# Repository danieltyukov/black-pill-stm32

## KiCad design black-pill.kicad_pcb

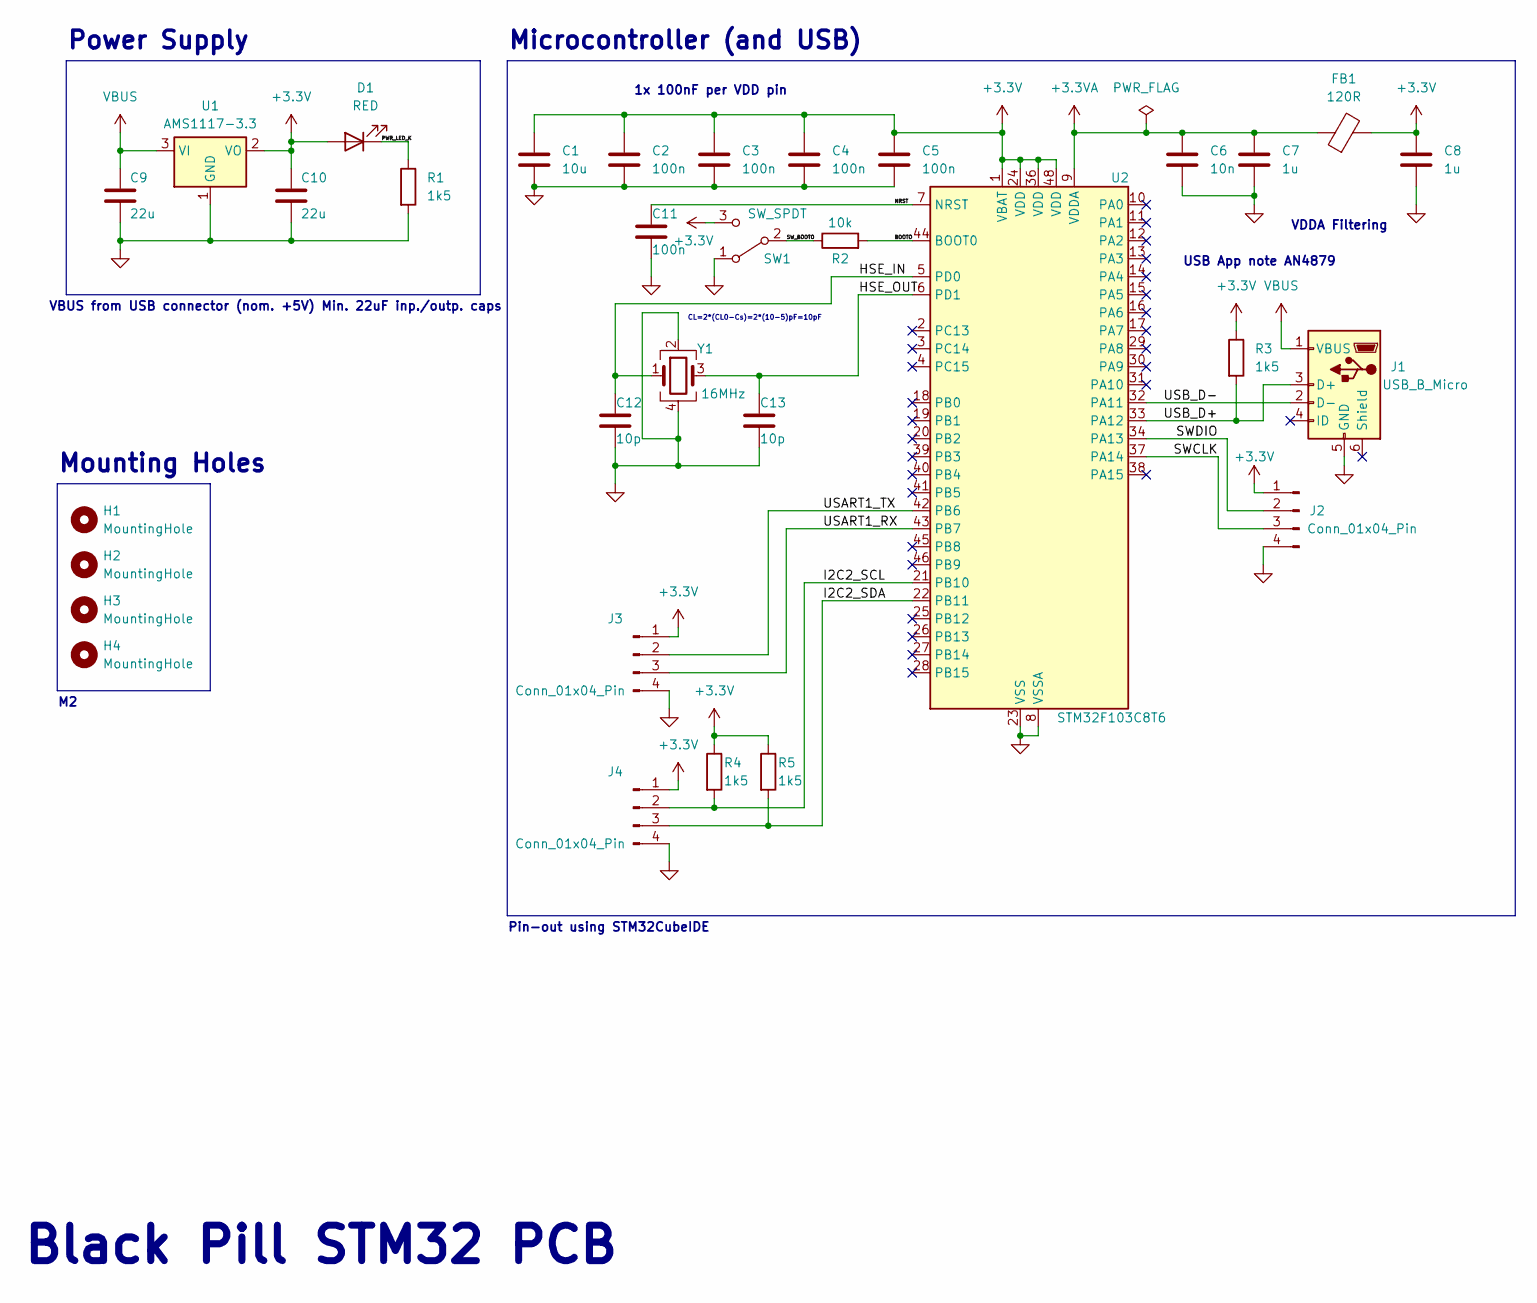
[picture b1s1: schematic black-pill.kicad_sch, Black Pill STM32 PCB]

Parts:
C1: 10u; C_0603_1608Metric
C2, C3, C4, C5, C11: 100n; C_0402_1005Metric
C6: 10n; C_0402_1005Metric
C7, C8: 1u; C_0402_1005Metric
C9, C10: 22u; C_0805_2012Metric
C12, C13: 10p; C_0402_1005Metric
D1: RED; LED_0603_1608Metric
FB1: 120R; L_0603_1608Metric
H1, H2, H3, H4: MountingHole; MountingHole_2.2mm_M2
J1: USB_B_Micro; USB_Micro-B_Wuerth_629105150521
J2, J3, J4: Conn_01x04_Pin; PinHeader_1x04_P2.54mm_Vertical
R1, R3, R4, R5: 1k5; R_0402_1005Metric
R2: 10k; C_0402_1005Metric
SW1: SW_SPDT; SW_SPDT_PCM12
U1: AMS1117-3.3; SOT-223-3_TabPin2
U2: STM32F103C8T6; LQFP-48_7x7mm_P0.5mm
Y1: 16MHz; Crystal_SMD_3225-4Pin_3.2x2.5mm

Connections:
+3.3V: C1.1, C2.1, C3.1, C4.1, C5.1, C8.1, C10.1, D1.2 (A), FB1.2, J2.1, J3.1, J4.1, R3.1, R4.1, R5.1, SW1.3 (C), U1.2 (VO), U2.1 (VBAT), U2.24 (VDD), U2.36 (VDD), U2.48 (VDD)
+3.3VA: C6.1, C7.1, FB1.1, U2.9 (VDDA)
/BOOTO: R2.2, U2.44 (BOOT0)
/HSE_IN: C12.1, U2.5 (PD0), Y1.1
/HSE_OUT: C13.1, U2.6 (PD1), Y1.3
/I2C2_SCL: J4.2, R4.2, U2.21 (PB10)
/I2C2_SDA: J4.3, R5.2, U2.22 (PB11)
/NRST: C11.1, U2.7 (NRST)
/PWR_LED_K: D1.1 (K), R1.1
/SWCLK: J2.3, U2.37 (PA14)
/SWDIO: J2.2, U2.34 (PA13)
/SW_BOOTO: R2.1, SW1.2 (B)
/USART1_RX: J3.3, U2.43 (PB7)
/USART1_TX: J3.2, U2.42 (PB6)
/USB_D+: J1.3 (D+), R3.2, U2.33 (PA12)
/USB_D-: J1.2 (D-), U2.32 (PA11)
GND: C1.2, C2.2, C3.2, C4.2, C5.2, C6.2, C7.2, C8.2, C9.2, C10.2, C11.2, C12.2, C13.2, J1.5 (GND), J2.4, J3.4, J4.4, R1.2, SW1.1 (A), U1.1 (GND), U2.8 (VSSA), U2.23 (VSS), U2.35 (VSS), U2.47 (VSS), Y1.2, Y1.4
VBUS: C9.1, J1.1 (VBUS), U1.3 (VI)

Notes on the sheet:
1x 100nF per VDD pin
VDDA Filtering
Pin-out using STM32CubeIDE
Power Supply
USB App note AN4879
CL=2*(CL0-Cs)=2*(10-5)pF=10pF
Microcontroller (and USB)
Mounting Holes
Black Pill STM32 PCB
VBUS from USB connector (nom. +5V) Min. 22uF inp./outp. caps

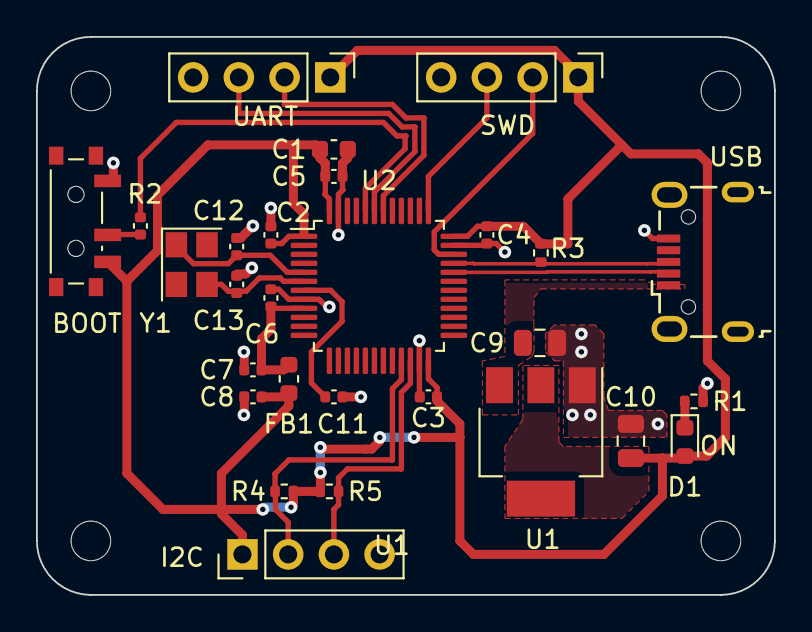
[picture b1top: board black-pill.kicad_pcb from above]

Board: 2 copper layers, 41.0 x 31.0 mm, 32 parts (0 on the bottom side), 18 nets.
